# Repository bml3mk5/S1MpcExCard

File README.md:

# Extension Card for HITACHI MB-S1

This is the extension card for HITACHI MB-S1 and Limelight.

## MPC_EX1

Extension Card for HITACHI MB-S1/10 and 20.

This card has two slots (edge connectors).

### Used Tools

* KiCAD Version 6

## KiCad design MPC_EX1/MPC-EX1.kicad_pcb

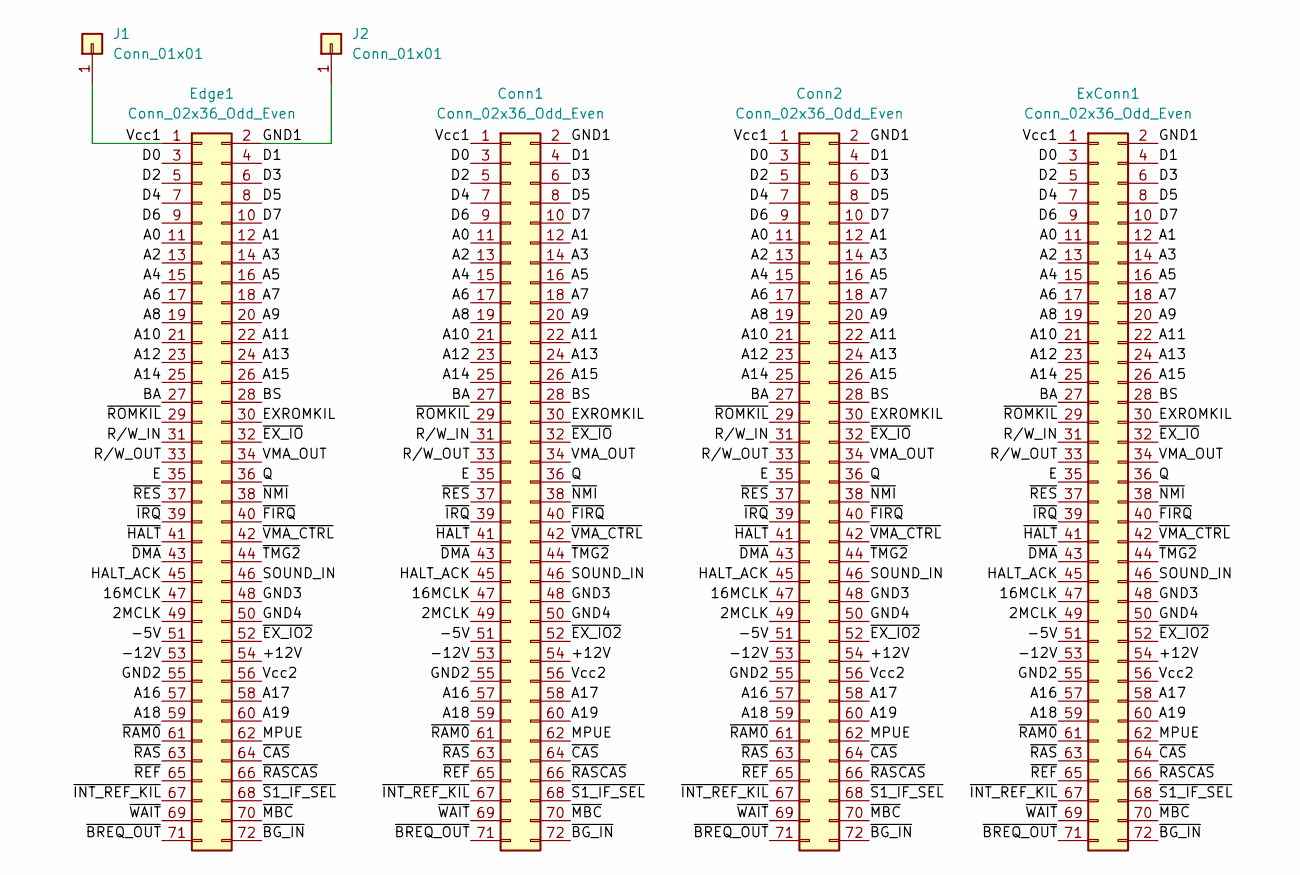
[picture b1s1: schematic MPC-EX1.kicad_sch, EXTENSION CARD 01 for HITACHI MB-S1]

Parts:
Conn1, Conn2: Conn_02x36_Odd_Even; MyConn_2x36_2.54
Edge1: Conn_02x36_Odd_Even; CardEdge72T
ExConn1: Conn_02x36_Odd_Even; PinSocket_2x36_P2.54mm_Horizontal
J1, J2: Conn_01x01; MyPad_1

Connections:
/2MCLK: Conn1.49, Conn2.49, Edge1.49, ExConn1.49
/16MCLK: Conn1.47, Conn2.47, Edge1.47, ExConn1.47
/+12V: Conn1.54, Conn2.54, Edge1.54, ExConn1.54
/-5V: Conn1.51, Conn2.51, Edge1.51, ExConn1.51
/-12V: Conn1.53, Conn2.53, Edge1.53, ExConn1.53
/A0: Conn1.11, Conn2.11, Edge1.11, ExConn1.11
/A1: Conn1.12, Conn2.12, Edge1.12, ExConn1.12
/A2: Conn1.13, Conn2.13, Edge1.13, ExConn1.13
/A3: Conn1.14, Conn2.14, Edge1.14, ExConn1.14
/A4: Conn1.15, Conn2.15, Edge1.15, ExConn1.15
/A5: Conn1.16, Conn2.16, Edge1.16, ExConn1.16
/A6: Conn1.17, Conn2.17, Edge1.17, ExConn1.17
/A7: Conn1.18, Conn2.18, Edge1.18, ExConn1.18
/A8: Conn1.19, Conn2.19, Edge1.19, ExConn1.19
/A9: Conn1.20, Conn2.20, Edge1.20, ExConn1.20
/A10: Conn1.21, Conn2.21, Edge1.21, ExConn1.21
/A11: Conn1.22, Conn2.22, Edge1.22, ExConn1.22
/A12: Conn1.23, Conn2.23, Edge1.23, ExConn1.23
/A13: Conn1.24, Conn2.24, Edge1.24, ExConn1.24
/A14: Conn1.25, Conn2.25, Edge1.25, ExConn1.25
/A15: Conn1.26, Conn2.26, Edge1.26, ExConn1.26
/A16: Conn1.57, Conn2.57, Edge1.57, ExConn1.57
/A17: Conn1.58, Conn2.58, Edge1.58, ExConn1.58
/A18: Conn1.59, Conn2.59, Edge1.59, ExConn1.59
/A19: Conn1.60, Conn2.60, Edge1.60, ExConn1.60
/BA: Conn1.27, Conn2.27, Edge1.27, ExConn1.27
/BS: Conn1.28, Conn2.28, Edge1.28, ExConn1.28
/D0: Conn1.3, Conn2.3, Edge1.3, ExConn1.3
/D1: Conn1.4, Conn2.4, Edge1.4, ExConn1.4
/D2: Conn1.5, Conn2.5, Edge1.5, ExConn1.5
/D3: Conn1.6, Conn2.6, Edge1.6, ExConn1.6
/D4: Conn1.7, Conn2.7, Edge1.7, ExConn1.7
/D5: Conn1.8, Conn2.8, Edge1.8, ExConn1.8
/D6: Conn1.9, Conn2.9, Edge1.9, ExConn1.9
/D7: Conn1.10, Conn2.10, Edge1.10, ExConn1.10
/E: Conn1.35, Conn2.35, Edge1.35, ExConn1.35
/EXROMKIL: Conn1.30, Conn2.30, Edge1.30, ExConn1.30
/GND1: Conn1.2, Conn2.2, Edge1.2, ExConn1.2, J2.1
/GND2: Conn1.55, Conn2.55, Edge1.55, ExConn1.55
/GND3: Conn1.48, Conn2.48, Edge1.48, ExConn1.48
/GND4: Conn1.50, Conn2.50, Edge1.50, ExConn1.50
/HALT_ACK: Conn1.45, Conn2.45, Edge1.45, ExConn1.45
/MPUE: Conn1.62, Conn2.62, Edge1.62, ExConn1.62
/Q: Conn1.36, Conn2.36, Edge1.36, ExConn1.36
/R/W_IN: Conn1.31, Conn2.31, Edge1.31, ExConn1.31
/R/W_OUT: Conn1.33, Conn2.33, Edge1.33, ExConn1.33
/SOUND_IN: Conn1.46, Conn2.46, Edge1.46, ExConn1.46
/VMA_OUT: Conn1.34, Conn2.34, Edge1.34, ExConn1.34
/Vcc1: Conn1.1, Conn2.1, Edge1.1, ExConn1.1, J1.1
/Vcc2: Conn1.56, Conn2.56, Edge1.56, ExConn1.56
/~BG_IN: Conn1.72, Conn2.72, Edge1.72, ExConn1.72
/~BREQ_OUT: Conn1.71, Conn2.71, Edge1.71, ExConn1.71
/~CAS: Conn1.64, Conn2.64, Edge1.64, ExConn1.64
/~DMA: Conn1.43, Conn2.43, Edge1.43, ExConn1.43
/~EX_IO2: Conn1.52, Conn2.52, Edge1.52, ExConn1.52
/~EX_IO: Conn1.32, Conn2.32, Edge1.32, ExConn1.32
/~FIRQ: Conn1.40, Conn2.40, Edge1.40, ExConn1.40
/~HALT: Conn1.41, Conn2.41, Edge1.41, ExConn1.41
/~INT_REF_KIL: Conn1.67, Conn2.67, Edge1.67, ExConn1.67
/~IRQ: Conn1.39, Conn2.39, Edge1.39, ExConn1.39
/~MBC: Conn1.70, Conn2.70, Edge1.70, ExConn1.70
/~NMI: Conn1.38, Conn2.38, Edge1.38, ExConn1.38
/~RAM0: Conn1.61, Conn2.61, Edge1.61, ExConn1.61
/~RASCAS: Conn1.66, Conn2.66, Edge1.66, ExConn1.66
/~RAS: Conn1.63, Conn2.63, Edge1.63, ExConn1.63
/~REF: Conn1.65, Conn2.65, Edge1.65, ExConn1.65
/~RES: Conn1.37, Conn2.37, Edge1.37, ExConn1.37
/~ROMKIL: Conn1.29, Conn2.29, Edge1.29, ExConn1.29
/~S1_IF_SEL: Conn1.68, Conn2.68, Edge1.68, ExConn1.68
/~TMG2: Conn1.44, Conn2.44, Edge1.44, ExConn1.44
/~VMA_CTRL: Conn1.42, Conn2.42, Edge1.42, ExConn1.42
/~WAIT: Conn1.69, Conn2.69, Edge1.69, ExConn1.69

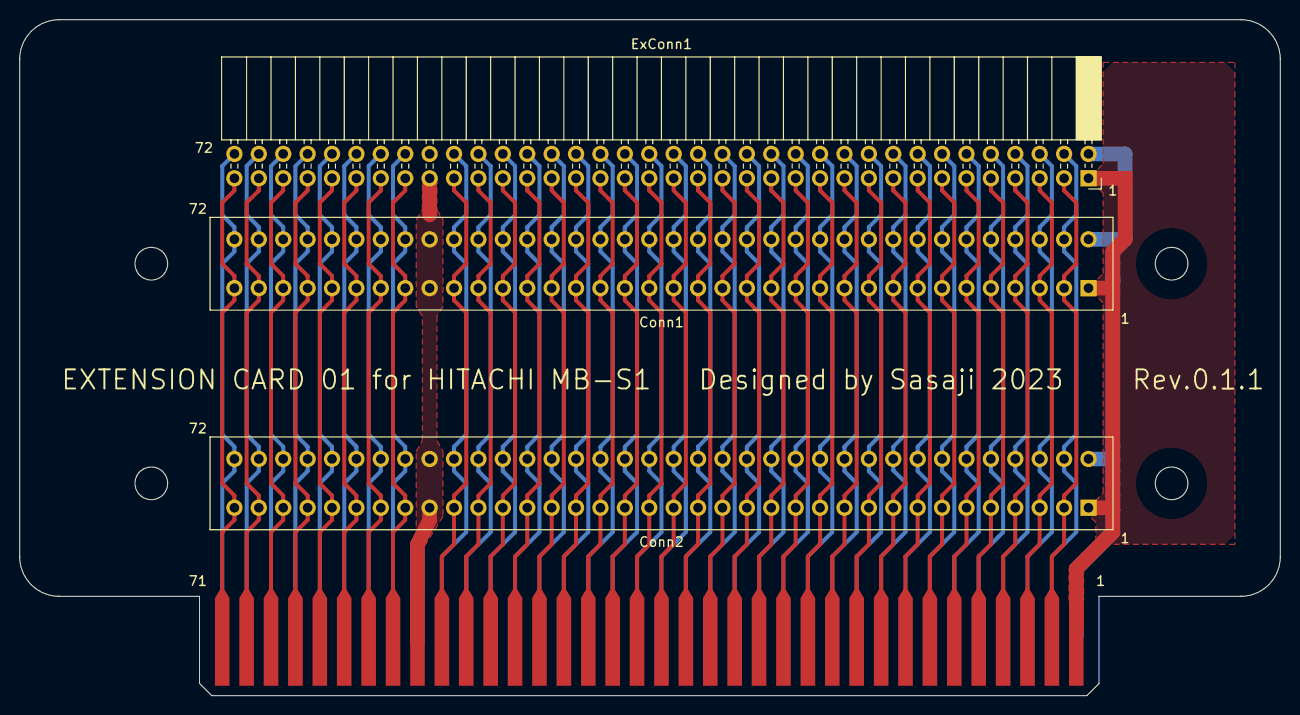
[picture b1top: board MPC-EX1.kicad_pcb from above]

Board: 2 copper layers, 131.2 x 70.4 mm, 6 parts (1 on the bottom side), 72 nets.

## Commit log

2023-05-20 Add MPC-EX1
2023-05-20 Modify documents
